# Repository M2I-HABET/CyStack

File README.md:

# CyStack

This is the electronics stack and associated software for a module payload stack

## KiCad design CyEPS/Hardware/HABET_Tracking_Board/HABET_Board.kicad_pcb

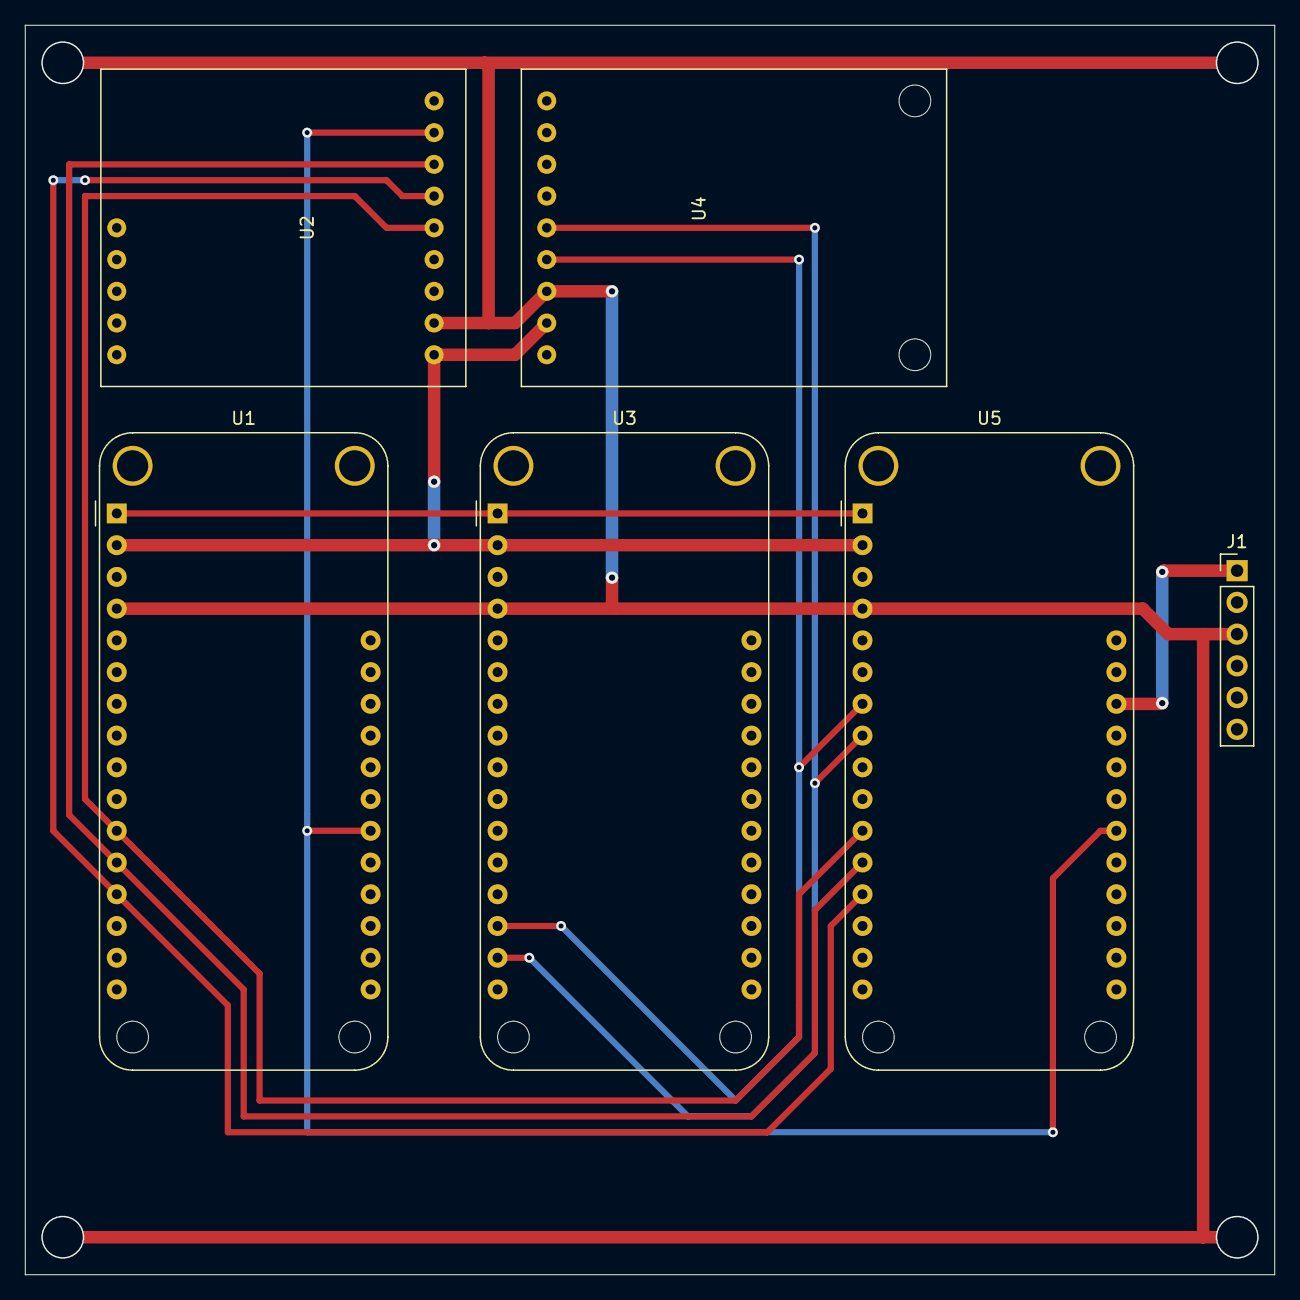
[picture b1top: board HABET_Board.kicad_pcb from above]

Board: 2 copper layers, 100.0 x 100.0 mm, 6 parts (0 on the bottom side), 10 nets.

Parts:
J1: Conn_01x06_Female; PinHeader_1x06_P2.54mm_Vertical
U1: LoRa Feather; Adafruit_Feather_WithMountingHoles
U2: LoRa_Breakout
U3: GPS Feather; Adafruit_Feather_WithMountingHoles
U4: GPS_Breakout
U5: M4; Adafruit_Feather_WithMountingHoles

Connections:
+3V3: U1.2, U2.1, U3.2, U4.8, U5.2
+5V: J1.1, U5.26
CS1: U1.22, U2.8, U5.22
GND: J1.3, U1.4, U2.2, U3.4, U4.7, U5.4
MISO: U1.13, U2.6, U5.13
MOSI: U1.12, U2.7, U5.12
Recieve: U3.15, U4.5, U5.8
Reset: U1.1, U3.1, U5.1
SCK: U1.11, U2.5, U5.11
Transmit: U3.14, U4.6, U5.7

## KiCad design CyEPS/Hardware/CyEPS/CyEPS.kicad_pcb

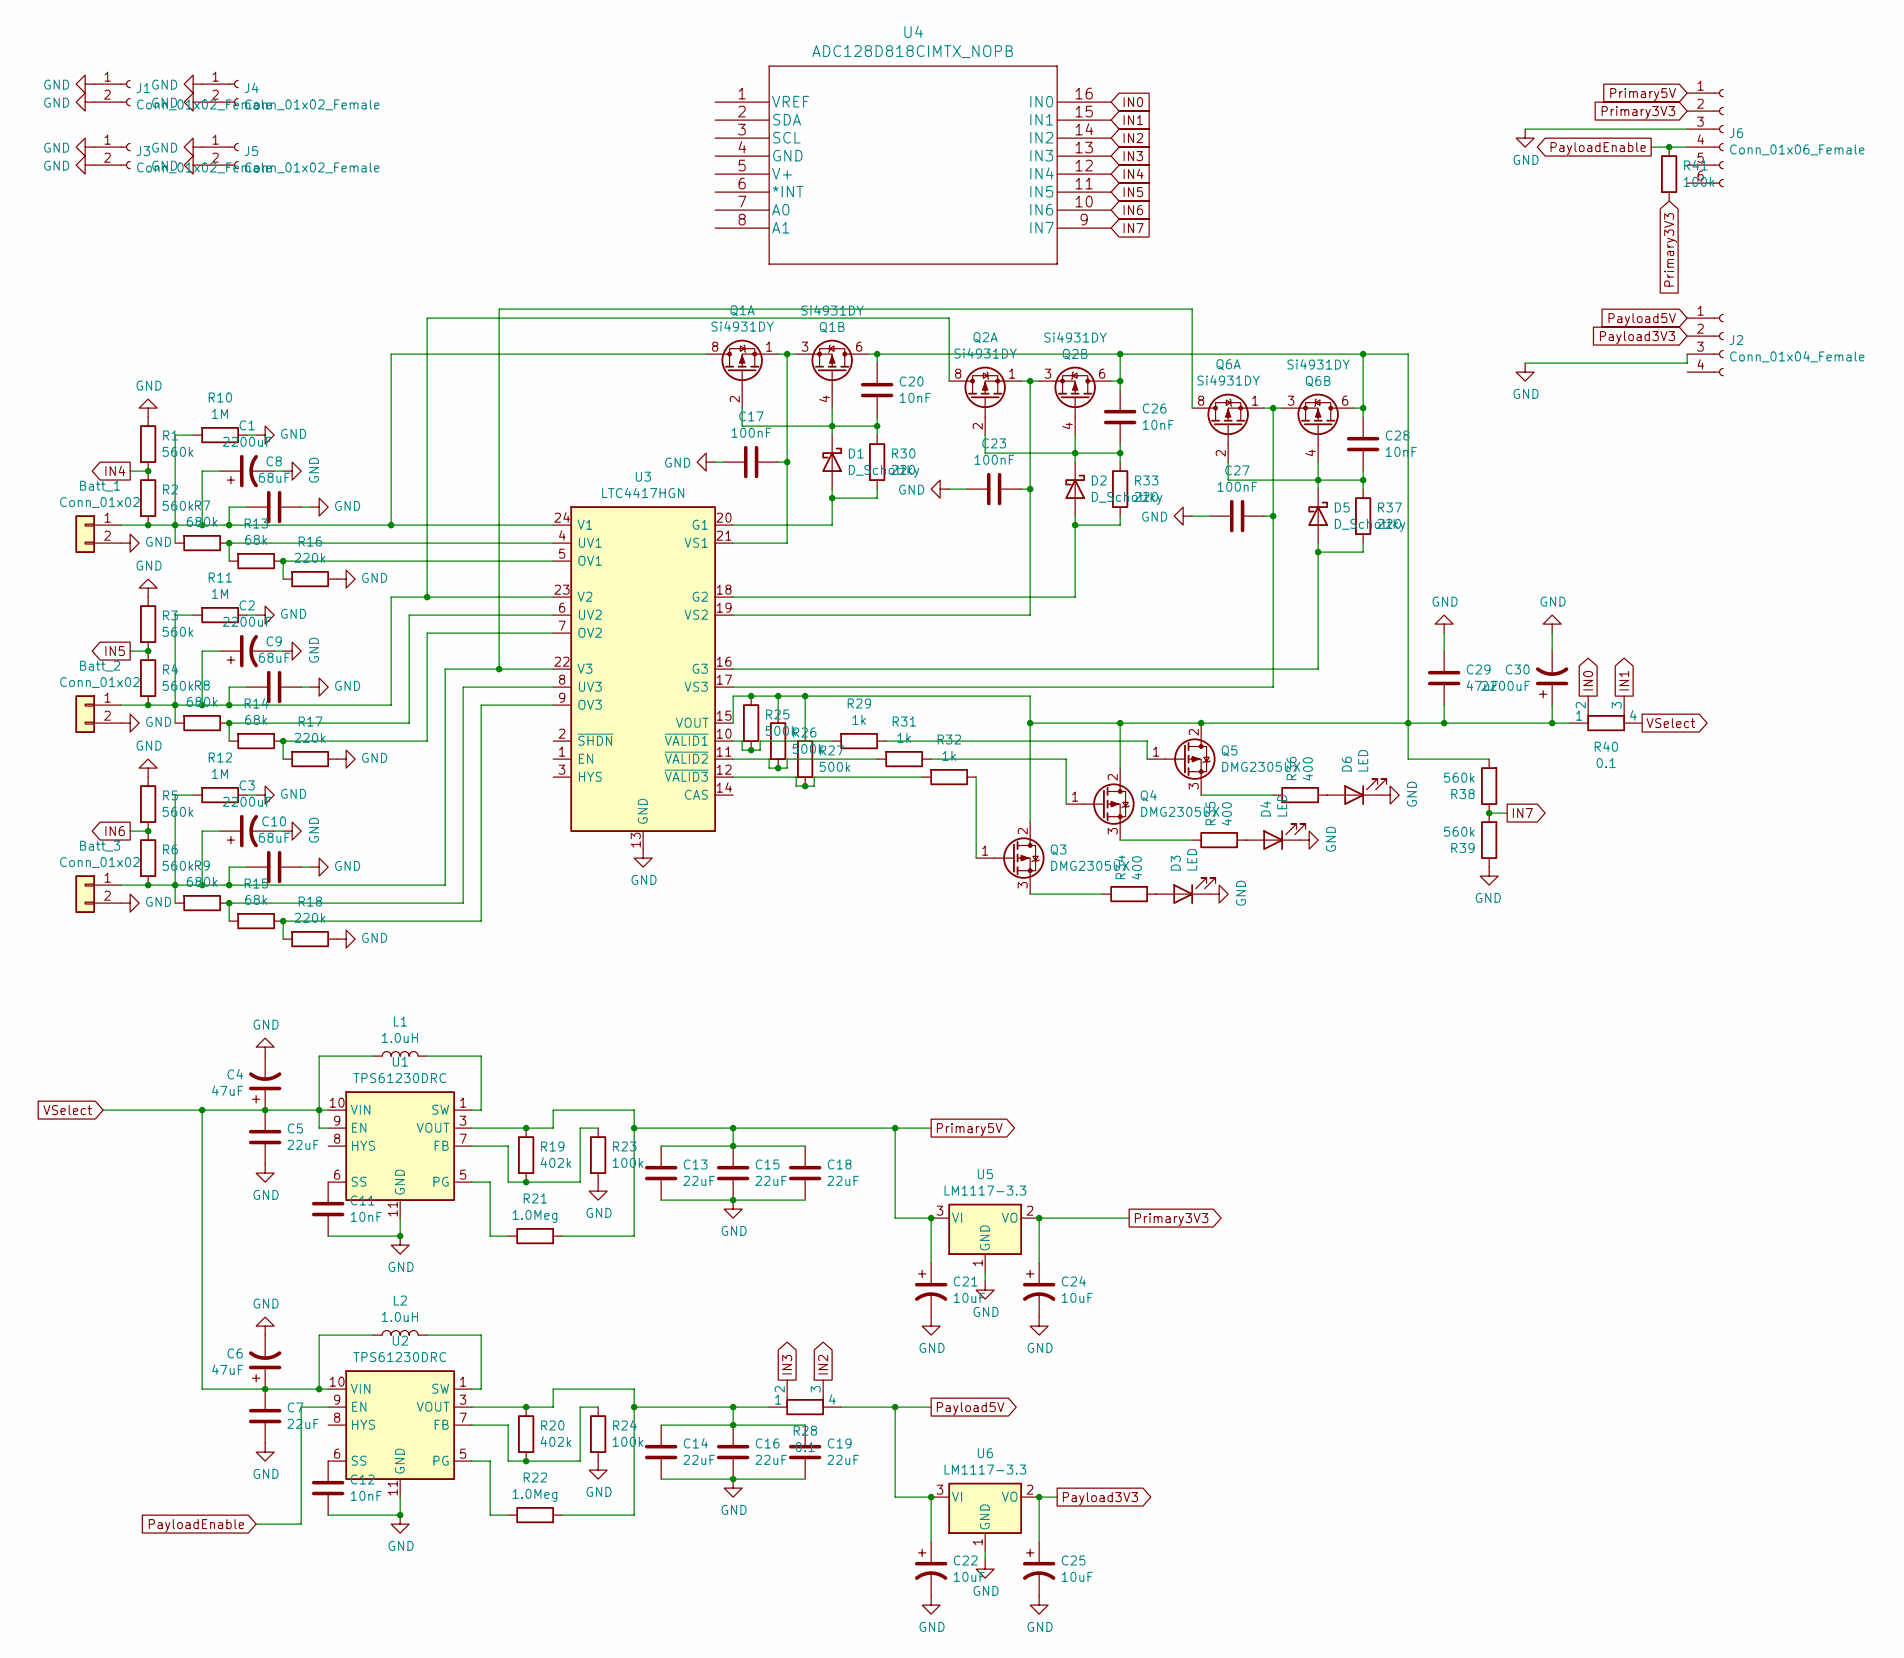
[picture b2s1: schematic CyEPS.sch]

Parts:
Batt_1: Conn_01x02; SolderWire-0.127sqmm_1x02_P3.7mm_D0.48mm_OD1mm
Batt_2, Batt_3: Conn_01x02; JST_PH_S2B-PH-K_1x02_P2.00mm_Horizontal
C1, C2, C3, C30: 2200uF; CP_EIA-1608-08_AVX-J_Pad1.25x1.05mm_HandSolder
C4, C6: 47uF; CP_EIA-1608-08_AVX-J_Pad1.25x1.05mm_HandSolder
C5, C7, C13, C14, C15, C16, C18, C19: 22uF; C_0805_2012Metric_Pad1.18x1.45mm_HandSolder
C8, C9, C10: 68uF; C_0805_2012Metric_Pad1.18x1.45mm_HandSolder
C11, C12, C20, C26, C28: 10nF; C_0805_2012Metric_Pad1.18x1.45mm_HandSolder
C17, C23, C27: 100nF; C_0805_2012Metric_Pad1.18x1.45mm_HandSolder
C21, C22, C24, C25: 10uF; CP_EIA-1608-08_AVX-J_Pad1.25x1.05mm_HandSolder
C29: 47uF; C_0805_2012Metric_Pad1.18x1.45mm_HandSolder
D1, D2, D5: D_Schottky; D_SOD-523
D3, D4, D6: LED; LED_0805_2012Metric_Pad1.15x1.40mm_HandSolder
J1, J3, J4, J5: Conn_01x02_Female; PinHeader_1x02_P2.54mm_Vertical
J2: Conn_01x04_Female; Molex_Micro-Fit_3.0_43650-0400_1x04_P3.00mm_Horizontal
J6: Conn_01x06_Female; PinHeader_1x06_P2.54mm_Vertical
L1, L2: 1.0uH; L_0805_2012Metric_Pad1.15x1.40mm_HandSolder
Q1, Q2, Q6: Si4931DY; SOIC-8_3.9x4.9mm_P1.27mm
Q3, Q4, Q5: DMG2305UX; TO-252-2
R1, R2, R3, R4, R5, R6, R38, R39: 560k; R_0805_2012Metric_Pad1.20x1.40mm_HandSolder
R7, R8, R9: 680k; R_0805_2012Metric_Pad1.20x1.40mm_HandSolder
R10, R11, R12: 1M; R_0805_2012Metric_Pad1.20x1.40mm_HandSolder
R13, R14, R15: 68k; R_0805_2012Metric_Pad1.20x1.40mm_HandSolder
R16, R17, R18: 220k; R_0805_2012Metric_Pad1.20x1.40mm_HandSolder
R19, R20: 402k; R_0805_2012Metric_Pad1.20x1.40mm_HandSolder
R21, R22: 1.0Meg; R_0805_2012Metric_Pad1.20x1.40mm_HandSolder
R23, R24, R41: 100k; R_0805_2012Metric_Pad1.20x1.40mm_HandSolder
R25, R26, R27: 500k; R_0805_2012Metric_Pad1.20x1.40mm_HandSolder
R28, R40: 0.1; R_Shunt_Ohmite_LVK12
R29, R31, R32: 1k; R_0805_2012Metric_Pad1.20x1.40mm_HandSolder
R30, R33, R37: 220; R_0805_2012Metric_Pad1.20x1.40mm_HandSolder
R34, R35, R36: 400; R_0805_2012Metric_Pad1.20x1.40mm_HandSolder
U1, U2: TPS61230DRC; Texas_S-PVSON-N10_ThermalVias
U3: LTC4417HGN; SSOP-24_3.9x8.7mm_P0.635mm
U4: ADC128D818CIMTX_NOPB; ADC128D818CIMTX&slash_NOPB
U5, U6: LM1117-3.3; SOT-223

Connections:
GND: Batt_1.2, Batt_2.2, Batt_3.2, C1.2, C2.2, C3.2, C4.2, C5.2, C6.2, C7.2, C8.1, C9.1, C10.1, C11.2, C12.2, C13.2, C14.2, C15.2, C16.2, C17.2, C18.2, C19.2, C21.2, C22.2, C23.2, C24.2, C25.2, C27.2, C29.1, C30.2, D3.1 (K), D4.1 (K), D6.1 (K), J1.1, J1.2, J2.3, J3.1, J3.2, J4.1, J4.2, J5.1, J5.2, J6.3, R1.1, R3.1, R5.1, R10.1, R11.1, R12.1, R16.1, R17.1, R18.1, R23.2, R24.2, R39.1, U1.11 (GND), U2.11 (GND), U3.13 (GND), U5.1 (GND), U6.1 (GND)
IN0: R40.2, U4.16 (IN0)
IN1: R40.3, U4.15 (IN1)
IN2: R28.3, U4.14 (IN2)
IN3: R28.2, U4.13 (IN3)
IN4: R1.2, R2.1, U4.12 (IN4)
IN5: R3.2, R4.1, U4.11 (IN5)
IN6: R5.2, R6.1, U4.10 (IN6)
IN7: R38.1, R39.2, U4.9 (IN7)
unnamed: Batt_1.1, C1.1, C8.2, Q1.7 (D1), Q1.8 (D1), R2.2, R7.2, R10.2, U3.24 (V1)
unnamed: Batt_2.1, C2.1, C9.2, Q2.7 (D1), Q2.8 (D1), R4.2, R8.2, R11.2, U3.23 (V2)
unnamed: Batt_3.1, C3.1, C10.2, Q6.7 (D1), Q6.8 (D1), R6.2, R9.2, R12.2, U3.22 (V3)
unnamed: C11.1, U1.6 (SS)
unnamed: C12.1, U2.6 (SS)
unnamed: C14.1, C16.1, C19.1, R20.1, R22.2, R28.1, U2.3 (VOUT), U2.4 (VOUT)
unnamed: C17.1, Q1.1 (S1), Q1.3 (S2), U3.21 (VS1)
unnamed: C20.1, C26.1, C28.1, C29.2, C30.1, Q1.5 (D2), Q1.6 (D2), Q2.5 (D2), Q2.6 (D2), Q3.2 (D), Q4.2 (D), Q5.2 (D), Q6.5 (D2), Q6.6 (D2), R25.1, R26.1, R27.1, R38.2, R40.1, U3.15 (VOUT)
unnamed: C20.2, D1.1 (K), Q1.2 (G1), Q1.4 (G2), R30.1
unnamed: C23.1, Q2.1 (S1), Q2.3 (S2), U3.19 (VS2)
unnamed: C26.2, D2.1 (K), Q2.2 (G1), Q2.4 (G2), R33.1
unnamed: C27.1, Q6.1 (S1), Q6.3 (S2), U3.17 (VS3)
unnamed: C28.2, D5.1 (K), Q6.2 (G1), Q6.4 (G2), R37.1
unnamed: D1.2 (A), R30.2, U3.20 (G1)
unnamed: D2.2 (A), R33.2, U3.18 (G2)
unnamed: D3.2 (A), R34.2
unnamed: D4.2 (A), R35.2
unnamed: D5.2 (A), R37.2, U3.16 (G3)
unnamed: D6.2 (A), R36.2
unnamed: L1.2, U1.1 (SW), U1.2 (SW)
unnamed: L2.2, U2.1 (SW), U2.2 (SW)
unnamed: Q3.1 (G), R32.1
unnamed: Q3.3 (S), R34.1
unnamed: Q4.1 (G), R31.1
unnamed: Q4.3 (S), R35.1
unnamed: Q5.1 (G), R29.1
unnamed: Q5.3 (S), R36.1
unnamed: R13.1, R16.2, U3.5 (OV1)
unnamed: R7.1, R13.2, U3.4 (UV1)
unnamed: R14.1, R17.2, U3.7 (OV2)
unnamed: R8.1, R14.2, U3.6 (UV2)
unnamed: R15.1, R18.2, U3.9 (OV3)
unnamed: R9.1, R15.2, U3.8 (UV3)
unnamed: R19.2, R23.1, U1.7 (FB)
unnamed: R20.2, R24.1, U2.7 (FB)
unnamed: R21.1, U1.5 (PG)
unnamed: R22.1, U2.5 (PG)
unnamed: R25.2, R29.2, U3.10 (~VALID1)
unnamed: R26.2, R31.2, U3.11 (~VALID2)
unnamed: R27.2, R32.2, U3.12 (~VALID3)
Payload3V3: C25.1, J2.2, U6.2 (VO)
Payload5V: C22.1, J2.1, R28.4, U6.3 (VI)
PayloadEnable: J6.4, R41.1, U2.9 (EN)
Primary3V3: C24.1, J6.2, R41.2, U5.2 (VO)
Primary5V: C13.1, C15.1, C18.1, C21.1, J6.1, R19.1, R21.2, U1.3 (VOUT), U1.4 (VOUT), U5.3 (VI)
VSelect: C4.1, C5.1, C6.1, C7.1, L1.1, L2.1, R40.4, U1.9 (EN), U1.10 (VIN), U2.10 (VIN)

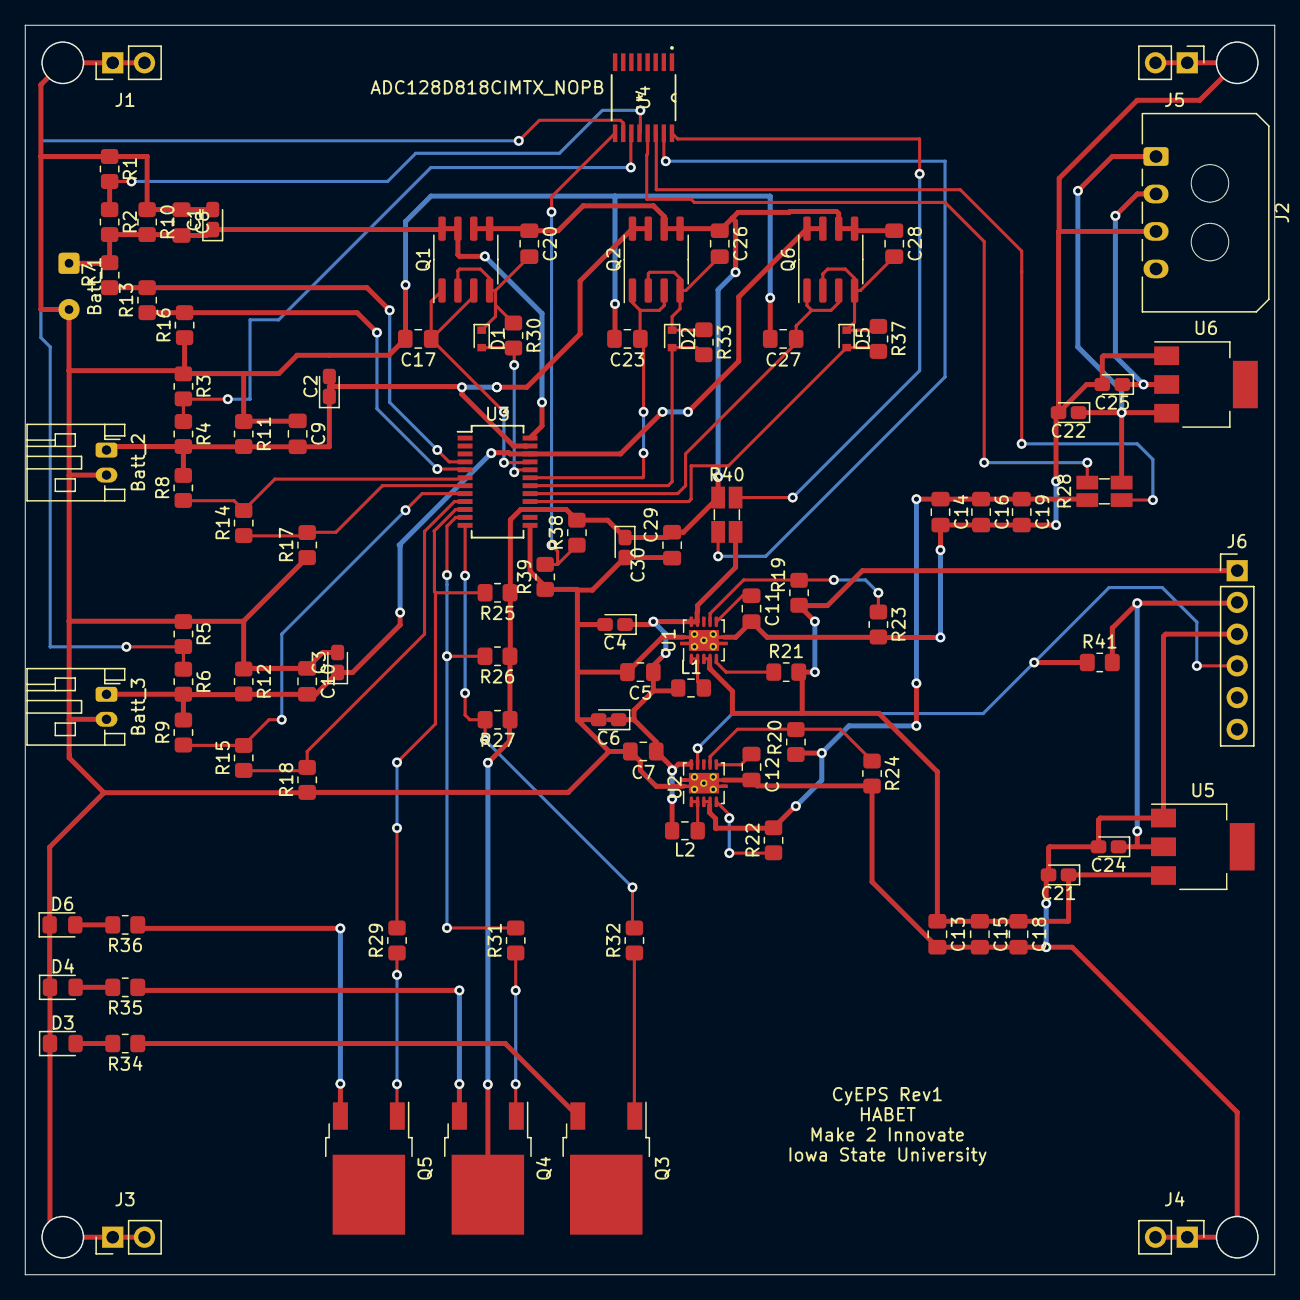
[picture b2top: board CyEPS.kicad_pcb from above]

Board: 2 copper layers, 100.0 x 100.0 mm, 100 parts (0 on the bottom side), 55 nets.

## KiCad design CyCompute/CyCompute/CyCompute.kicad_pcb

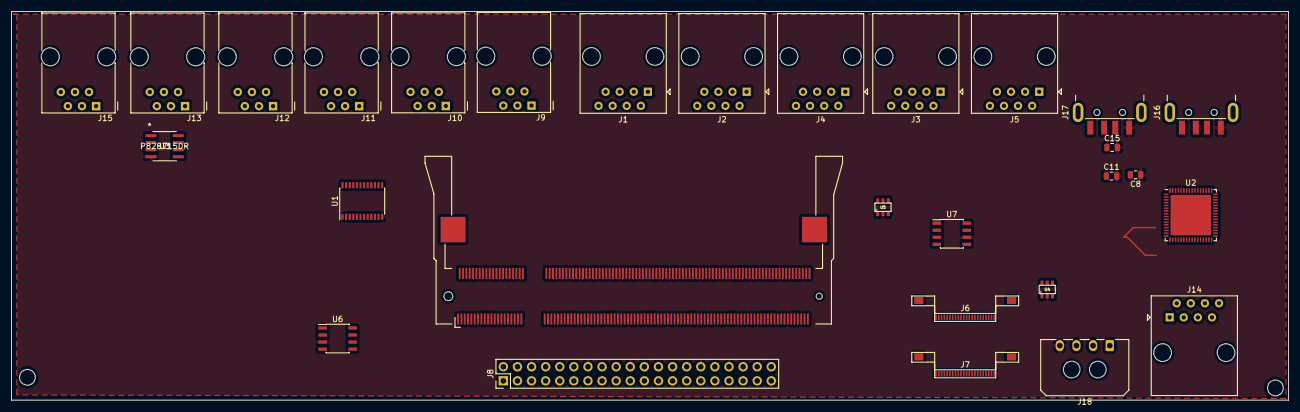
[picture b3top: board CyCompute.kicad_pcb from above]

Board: 2 copper layers, 230.0 x 70.0 mm, 29 parts (0 on the bottom side), 98 nets.

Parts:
C8: 15pf; C_0805_2012Metric
C11, C15: CAP100n; C_0805_2012Metric
J1, J2, J3, J4, J5, J14: RJ45; RJ45_Amphenol_54602-x08_Horizontal
J6: CAM0; FPC_22
J7: CAM1; FPC_22
J8: Pi Std header; PinHeader_2x20_P2.54mm_Vertical
J9, J10, J11, J12, J13, J15: RJ11; RJ12_Amphenol_54601
J16, J17: USB_A; USB_A_CNCTech_1001-011-01101_Horizontal
J18: Conn_01x04_Female; Molex_Micro-Fit_3.0_43650-0400_1x04_P3.00mm_Horizontal
MD1: Board_RPi_CM3lite_200pConnector; sodimm_pi
U1: TCA9548APWR; TSSOP-24_4.4x7.8mm_P0.65mm
U2: LAN9514; QFN-64-1EP_9x9mm_P0.5mm_EP7.3x7.3mm
U3: P82B715DR
U4, U5: IP4234CZ6; SOT457
U6: PAM2306AYPKE; SOIC-8_3.9x4.9mm_P1.27mm
U7: SP2526A-2EN-L; SOIC-8_3.9x4.9mm_P1.27mm

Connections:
+1V8: MD1.183, MD1.184, MD1.185, MD1.186
+3V3: J6.22, J7.22, J8.1, J8.17, J18.3, MD1.39, MD1.40, MD1.41, MD1.42, MD1.189, MD1.190, MD1.191, MD1.192, MD1.193, MD1.194, U1.24, U2.28, U2.29, U2.30, U2.32, U2.40, U3.8
+5V: J8.2, J8.4, J18.2, MD1.197, MD1.198, MD1.199, MD1.200, U6.1, U6.6, U6.7
CAM0_CN: J6.8, MD1.144
CAM0_CP: J6.9, MD1.142
CAM0_DN0: J6.2, MD1.138
CAM0_DN1: J6.5, MD1.150
CAM0_DP0: J6.3, MD1.136
CAM0_DP1: J6.6, MD1.148
CAM1_CN: J7.8, MD1.149
CAM1_CP: J7.9, MD1.147
CAM1_DN0: J7.2, MD1.161
CAM1_DN1: J7.5, MD1.155
CAM1_DN2: J7.11, MD1.143
CAM1_DN3: J7.14, MD1.137
CAM1_DP0: J7.3, MD1.159
CAM1_DP1: J7.6, MD1.153
CAM1_DP2: J7.12, MD1.141
CAM1_DP3: J7.15, MD1.135
GND: C8.1, C11.2, C15.2, J6.1, J6.4, J6.7, J6.10, J6.13, J6.16, J6.19, J7.1, J7.4, J7.7, J7.10, J7.13, J7.16, J7.19, J8.6, J8.9, J8.14, J8.20, J8.25, J8.30, J8.34, J8.39, J16.4, J17.4, J18.4, MD1.1, MD1.7, MD1.8, MD1.13, MD1.14, MD1.19, MD1.20, MD1.25, MD1.26, MD1.31, MD1.32, MD1.37, MD1.38, MD1.43, MD1.44, MD1.49, MD1.50, MD1.55, MD1.56, MD1.61, MD1.62, MD1.67, MD1.68, MD1.73, MD1.74, MD1.79, MD1.80, MD1.85, MD1.86, MD1.91, MD1.92, MD1.97, MD1.98, MD1.103, MD1.104, MD1.109, MD1.110, MD1.115, MD1.116, MD1.121, MD1.122, MD1.127, MD1.133, MD1.134, MD1.139, MD1.140, MD1.145, MD1.146, MD1.151, MD1.152, MD1.157, MD1.163, MD1.164, MD1.169, MD1.170, MD1.181, MD1.182, MD1.187, MD1.188, MD1.195, MD1.196, U1.1, U1.2, U1.12, U1.21, U2.34, U2.44, U2.65, U3.4, U4.2, U5.2, U6.3, U7.6
GPIO02: J8.3, MD1.9, U1.22
GPIO03: J8.5, MD1.11, U1.23
GPIO04: J8.7, MD1.15
GPIO05: J8.29, MD1.17
GPIO06: J8.31, MD1.21
GPIO07: J8.26, MD1.23
GPIO08: J8.24, MD1.27
GPIO09: J8.21, MD1.29
GPIO10: J8.19, MD1.33
GPIO11: J8.23, MD1.35
GPIO12: J8.32, MD1.45
GPIO13: J8.33, MD1.47
GPIO14: J8.8, MD1.51
GPIO15: J8.10, MD1.53
GPIO16: J8.36, MD1.57
GPIO17: J8.11, MD1.59
GPIO18: J8.12, MD1.63
GPIO19: J8.35, MD1.65
GPIO20: J8.38, MD1.69
GPIO21: J8.40, MD1.71
GPIO22: J8.15, MD1.75
GPIO23: J8.16, MD1.77
GPIO24: J8.18, MD1.81
GPIO25: J8.22, MD1.83
GPIO26: J8.37, MD1.87
GPIO27: J1.8, J8.13, MD1.89
GPIO28: J1.6, MD1.28
GPIO29: J1.4, MD1.30
GPIO30: J1.2, MD1.34
GPIO31: J2.8, MD1.36
GPIO32: J2.6, MD1.46
GPIO33: J2.4, MD1.48
GPIO34: J2.2, MD1.52
GPIO35: J3.8, MD1.54
GPIO36: J3.6, MD1.58
GPIO37: J3.4, MD1.60
GPIO38: J3.2, MD1.64
GPIO39: J4.8, MD1.66
GPIO41: J4.6, MD1.72
GPIO42: J4.4, MD1.76
GPIO43: J4.2, MD1.78
GPIO44: J5.8, MD1.82
GPIO45: J5.6, MD1.84
LX: J15.2, U3.2
LY: J15.1, U3.7
unnamed: J14.6, U2.53
unnamed: C8.2, J14.3, U2.52
unnamed: J14.2, U2.56
unnamed: J14.1, U2.55
unnamed: J9.1, U1.5
unnamed: J9.2, U1.4
unnamed: J10.1, U1.7
unnamed: J10.2, U1.6
unnamed: J11.1, U1.9
unnamed: J11.2, U1.8
unnamed: J12.1, U1.11
unnamed: J12.2, U1.10
unnamed: J13.1, U1.14
unnamed: J13.2, U1.13
PRTCTL2: U2.14, U7.1, U7.2
PRTCTL3: U2.16, U7.3, U7.4
SX: U1.19, U3.3
SY: U1.20, U3.6
USBDM0: MD1.167, U2.58
USBDM2: U2.1, U4.6
USBDM2Out: J16.2, U4.4
USBDM3: U2.3, U5.6
USBDM3Out: J17.2, U5.4
USBDP0: MD1.165, U2.59
USBDP2: U2.2, U4.1
USBDP2Out: J16.3, U4.3
USBDP3: U2.4, U5.1
USBDP3Out: J17.3, U5.3
VCC_USB_EX1: J16.1, U7.8
VCC_USB_EX2: J17.1, U7.5
VDD18CORE: U2.15, U2.38
VDD33A: C11.1, C15.1, U2.5, U2.10, U2.49, U2.51, U2.54, U2.57, U2.64
VDD33IO: U2.11, U2.19, U2.27, U2.33, U2.39, U2.46

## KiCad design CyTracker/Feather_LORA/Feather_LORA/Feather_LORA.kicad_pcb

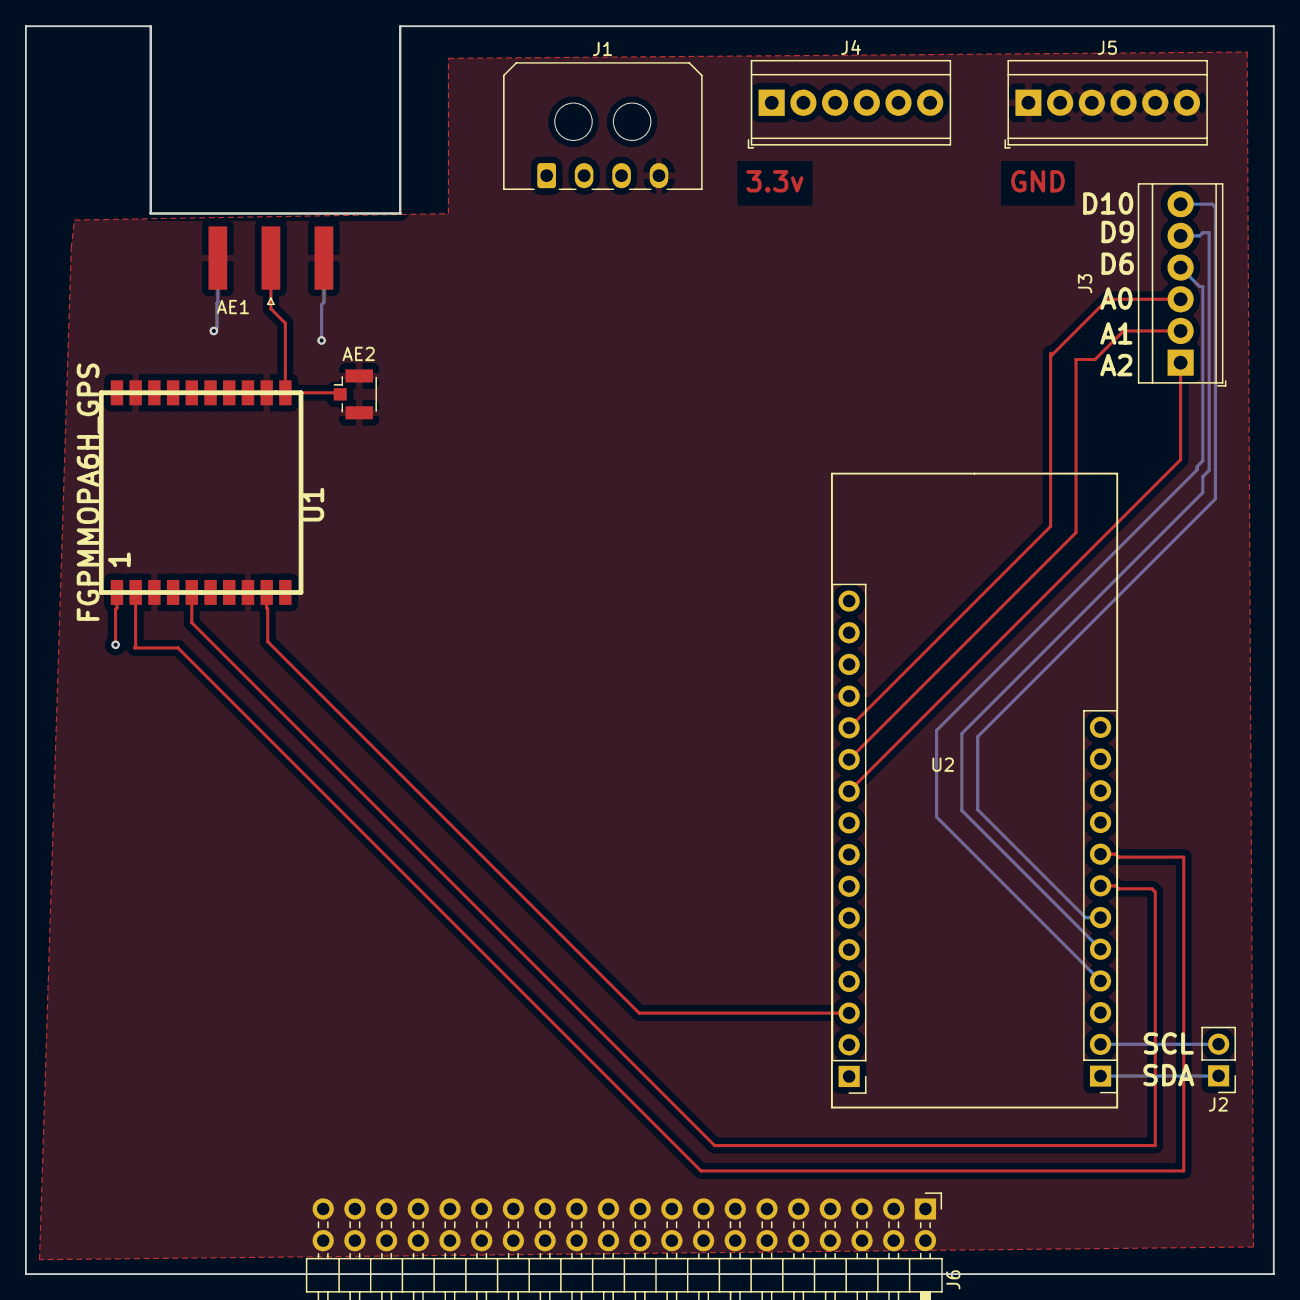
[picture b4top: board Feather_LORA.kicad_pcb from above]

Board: 2 copper layers, 100.0 x 100.0 mm, 10 parts (0 on the bottom side), 14 nets.

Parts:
AE1: Antenna_Shield; SMA_Amphenol_132289_EdgeMount
AE2: Antenna_Shield; U.FL_Hirose_U.FL-R-SMT-1_Vertical
J1: Conn_01x04_Female; Molex_Micro-Fit_3.0_43650-0400_1x04_P3.00mm_Horizontal
J2: Conn_01x02_Male; PinHeader_1x02_P2.54mm_Vertical
J3, J4, J5: Conn_01x06_Male; TerminalBlock_TE_282834-6_1x06_P2.54mm_Horizontal
J6: Conn_02x20_Top_Bottom; Pin_Header_Angled_2x20_Pitch2.54mm
U1: FGPMMOPA6H_GPS; FGPMMOPA6H
U2: Feather32u4RFM95; AdafruitFeather

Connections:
+3V3: J1.3, J4.1, J4.2, J4.3, J4.4, J4.5, J4.6, U1.1, U2.15
GND: AE1.2, AE2.2, J1.4, J5.1, J5.2, J5.3, J5.4, J5.5, J5.6, U1.3, U1.8, U1.12, U1.19, U2.13
unnamed: AE1.1, AE2.1, U1.11
unnamed: J2.1, U2.28
unnamed: J2.2, U2.27
unnamed: J3.1, U2.10
unnamed: J3.2, U2.11
unnamed: J3.3, U2.12
unnamed: J3.4, U2.25
unnamed: J3.5, U2.24
unnamed: J3.6, U2.23
unnamed: U1.2, U2.21
unnamed: U1.5, U2.22
unnamed: U1.9, U2.3

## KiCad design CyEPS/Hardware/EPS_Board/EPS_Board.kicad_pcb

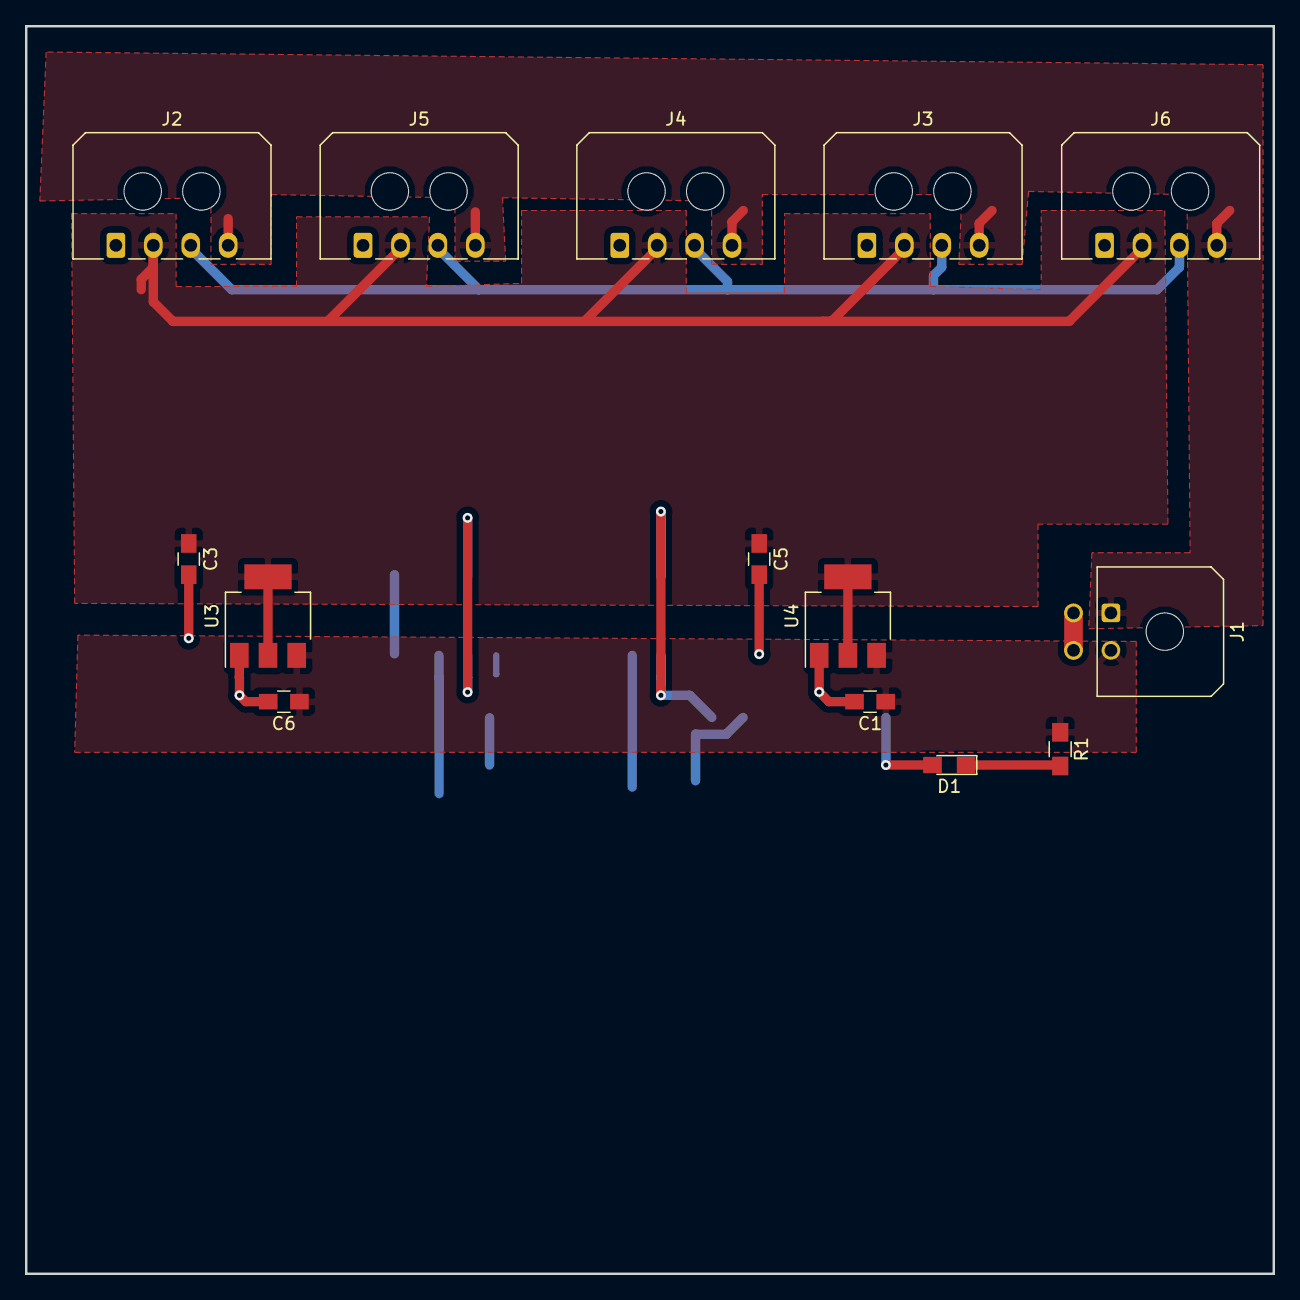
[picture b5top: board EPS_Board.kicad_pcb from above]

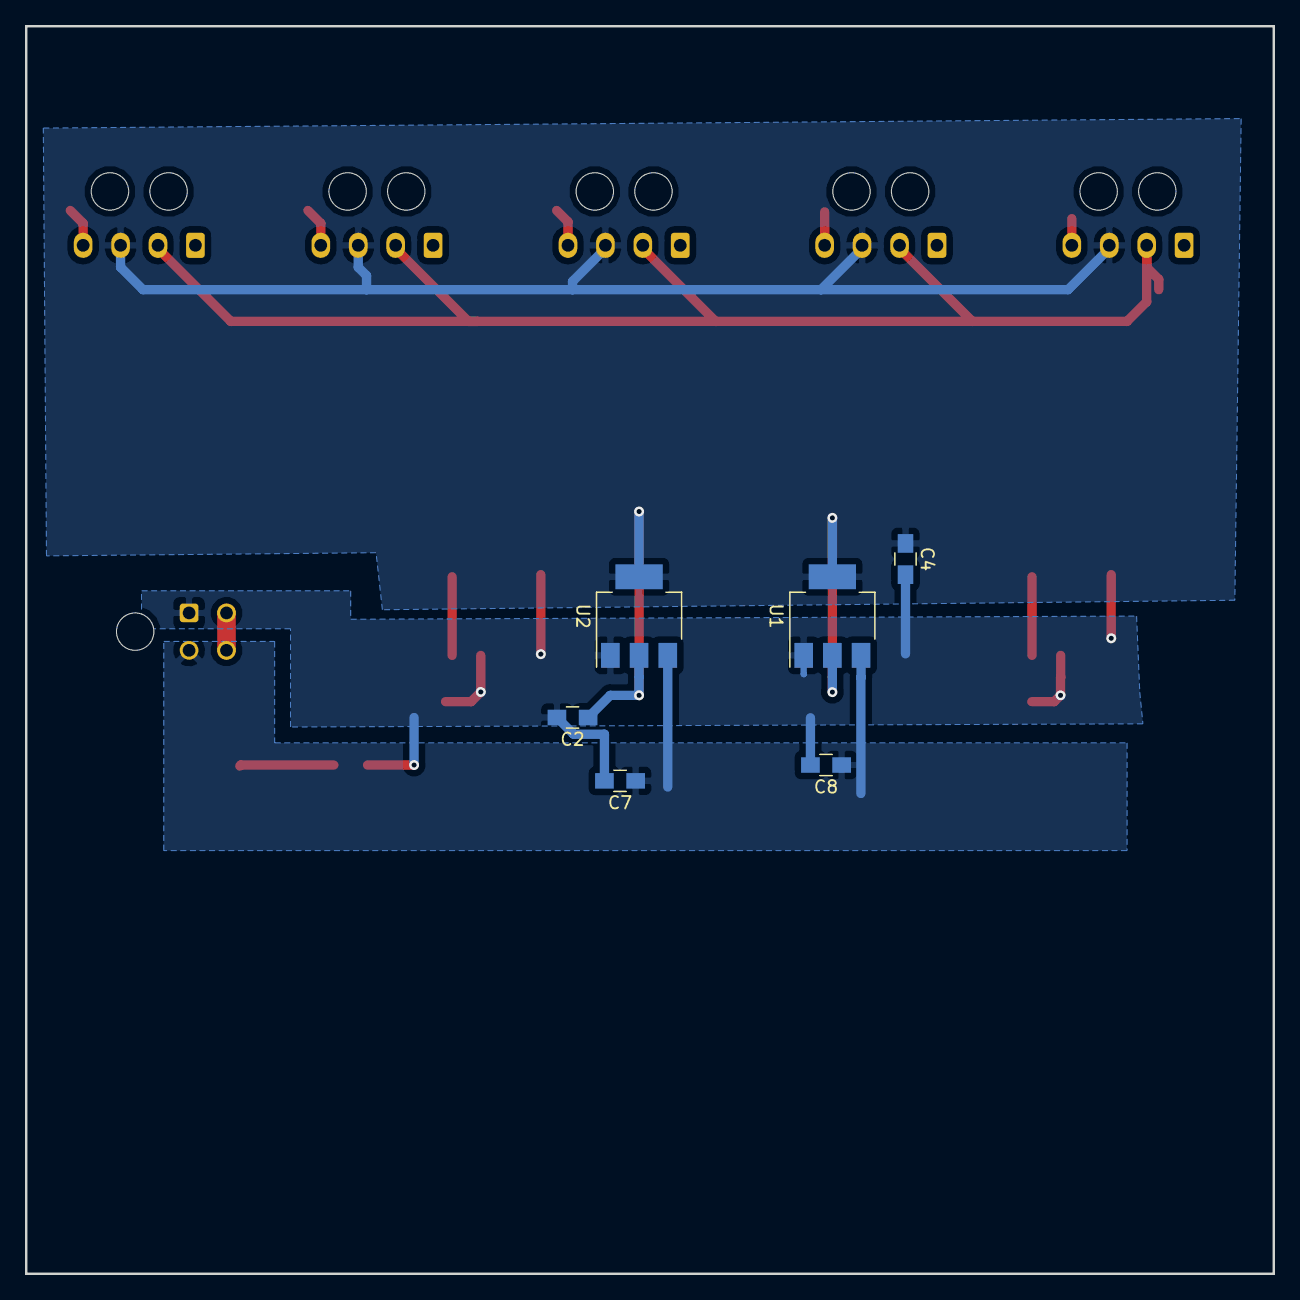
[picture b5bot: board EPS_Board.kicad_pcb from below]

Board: 2 copper layers, 100.0 x 100.0 mm, 20 parts (6 on the bottom side), 6 nets.

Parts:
C1, C2, C3, C4, C5, C6, C7, C8: CAP; C_0805_HandSoldering
D1: LED; LED_0805_HandSoldering
J1: Conn_02x02_Counter_Clockwise; Molex_Micro-Fit_3.0_43045-0400_2x02_P3.00mm_Horizontal
J2, J3, J4, J5, J6: Conn_01x04_Female; Molex_Micro-Fit_3.0_43650-0400_1x04_P3.00mm_Horizontal
R1: R; R_0805_HandSoldering
U1, U2: AZ1117-3.3; SOT-223-3_TabPin2
U3, U4: AZ1117-5.0; SOT-223-3_TabPin2

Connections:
+3V3: C2.1, C4.1, J2.3, J3.3, J4.3, J5.3, J6.3, U1.2, U2.2
+5V: C3.1, C5.1, J2.2, J3.2, J4.2, J5.2, J6.2, U3.2, U4.2
+BATT: C1.1, C6.1, C7.1, C8.1, J1.2, R1.1, U1.3, U2.3, U3.3, U4.3
GND: C1.2, C2.2, C3.2, C4.2, C5.2, C6.2, C7.2, C8.2, D1.2, J1.1, J2.4, J3.4, J4.4, J5.4, J6.4, U1.1, U2.1, U3.1, U4.1
unnamed: D1.1, R1.2
unnamed: J1.3, J1.4

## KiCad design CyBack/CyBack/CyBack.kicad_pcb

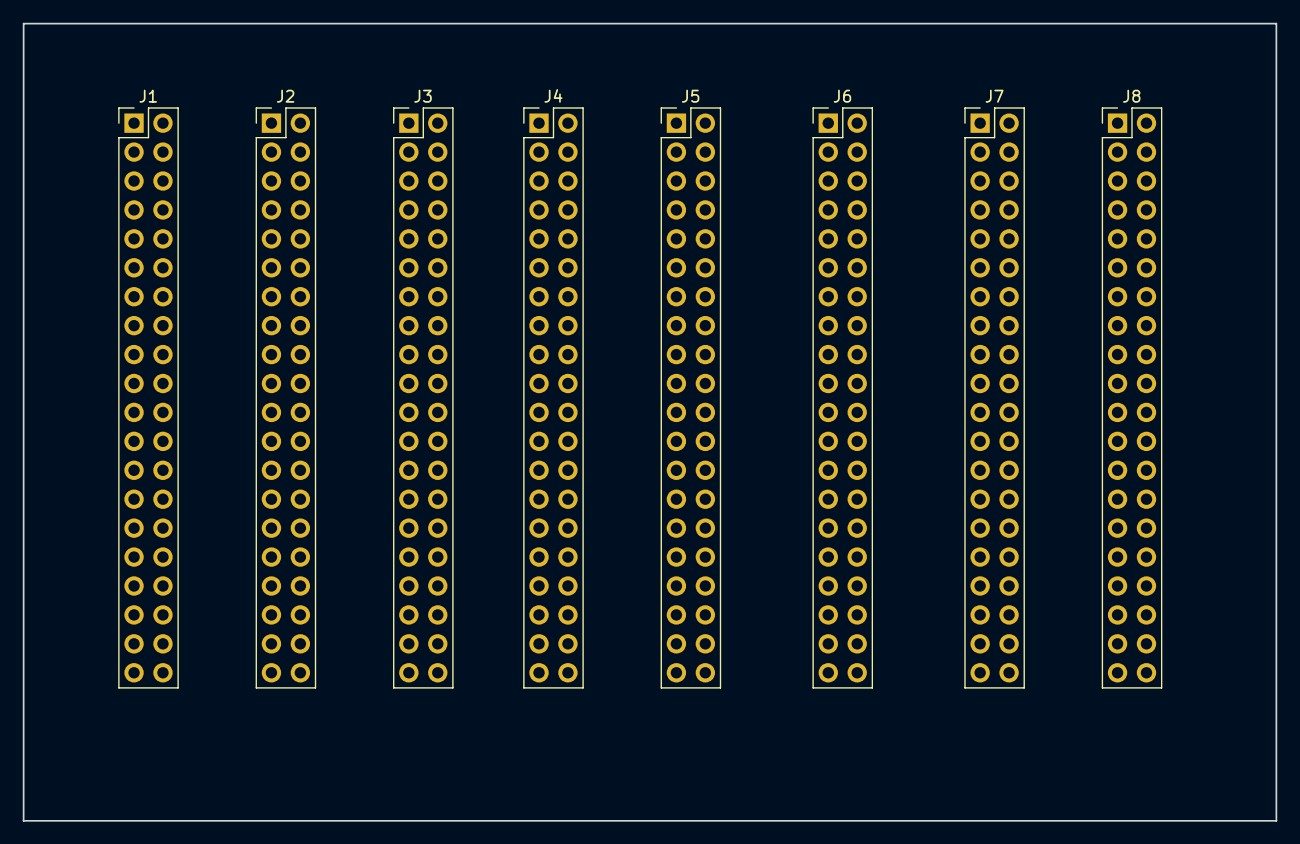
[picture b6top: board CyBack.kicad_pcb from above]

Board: 2 copper layers, 110.0 x 70.0 mm, 8 parts (0 on the bottom side), 40 nets, no tracks yet.

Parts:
J1, J2, J3, J4, J5, J6, J7, J8: Conn_02x20_Odd_Even; Pin_Header_Straight_2x20_Pitch2.54mm

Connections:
1: J1.3, J2.3, J3.3, J4.3, J5.3, J6.3, J7.3, J8.3
2: J1.5, J2.5, J3.5, J4.5, J5.5, J6.5, J7.5, J8.5
3: J1.7, J2.7, J3.7, J4.7, J5.7, J6.7, J7.7, J8.7
4: J1.9, J2.9, J3.9, J4.9, J5.9, J6.9, J7.9, J8.9
5: J1.11, J2.11, J3.11, J4.11, J5.11, J6.11, J7.11, J8.11
6: J1.13, J2.13, J3.13, J4.13, J5.13, J6.13, J7.13, J8.13
7: J1.15, J2.15, J3.15, J4.15, J5.15, J6.15, J7.15, J8.15
8: J1.17, J2.17, J3.17, J4.17, J5.17, J6.17, J7.17, J8.17
9: J1.19, J2.19, J3.19, J4.19, J5.19, J6.19, J7.19, J8.19
10: J1.21, J2.21, J3.21, J4.21, J5.21, J6.21, J7.21, J8.21
11: J1.23, J2.23, J3.23, J4.23, J5.23, J6.23, J7.23, J8.23
12: J1.25, J2.25, J3.25, J4.25, J5.25, J6.25, J7.25, J8.25
13: J1.27, J2.27, J3.27, J4.27, J5.27, J6.27, J7.27, J8.27
14: J1.29, J2.29, J3.29, J4.29, J5.29, J6.29, J7.29, J8.29
15: J1.31, J2.31, J3.31, J4.31, J5.31, J6.31, J7.31, J8.31
16: J1.33, J2.33, J3.33, J4.33, J5.33, J6.33, J7.33, J8.33
17: J1.35, J2.35, J3.35, J4.35, J5.35, J6.35, J7.35, J8.35
18: J1.37, J2.37, J3.37, J4.37, J5.37, J6.37, J7.37, J8.37
19: J1.39, J2.39, J3.39, J4.39, J5.39, J6.39, J7.39, J8.39
20: J1.2, J2.2, J3.2, J4.2, J5.2, J6.2, J7.2, J8.2
21: J1.4, J2.4, J3.4, J4.4, J5.4, J6.4, J7.4, J8.4
22: J1.6, J2.6, J3.6, J4.6, J5.6, J6.6, J7.6, J8.6
23: J1.8, J2.8, J3.8, J4.8, J5.8, J6.8, J7.8, J8.8
24: J1.10, J2.10, J3.10, J4.10, J5.10, J6.10, J7.10, J8.10
25: J1.12, J2.12, J3.12, J4.12, J5.12, J6.12, J7.12, J8.12
26: J1.14, J2.14, J3.14, J4.14, J5.14, J6.14, J7.14, J8.14
27: J1.16, J2.16, J3.16, J4.16, J5.16, J6.16, J7.16, J8.16
28: J1.18, J2.18, J3.18, J4.18, J5.18, J6.18, J7.18, J8.18
29: J1.20, J2.20, J3.20, J4.20, J5.20, J6.20, J7.20, J8.20
30: J1.22, J2.22, J3.22, J4.22, J5.22, J6.22, J7.22, J8.22
31: J1.24, J2.24, J3.24, J4.24, J5.24, J6.24, J7.24, J8.24
32: J1.26, J2.26, J3.26, J4.26, J5.26, J6.26, J7.26, J8.26
33: J1.28, J2.28, J3.28, J4.28, J5.28, J6.28, J7.28, J8.28
34: J1.30, J2.30, J3.30, J4.30, J5.30, J6.30, J7.30, J8.30
35: J1.32, J2.32, J3.32, J4.32, J5.32, J6.32, J7.32, J8.32
36: J1.34, J2.34, J3.34, J4.34, J5.34, J6.34, J7.34, J8.34
37: J1.36, J2.36, J3.36, J4.36, J5.36, J6.36, J7.36, J8.36
38: J1.38, J2.38, J3.38, J4.38, J5.38, J6.38, J7.38, J8.38
39: J1.40, J2.40, J3.40, J4.40, J5.40, J6.40, J7.40, J8.40
40: J1.1, J2.1, J3.1, J4.1, J5.1, J6.1, J7.1, J8.1

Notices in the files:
parts and their libraries:
Copyright 2016 Accelerated Designs. All rights reserved.
